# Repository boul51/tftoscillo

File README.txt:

This project is meant to make a pocket oscillator from an Arduino Due board along with a TFT screen.

To build,clean and run the project,
use associated Makefile targets in tftoscillo subfolder:
make, make clean, make run

You must have arduino-cli in your path (available from https://github.com/arduino/arduino-cli.git)

Note: Arduino IDE cannot be used to build the project because the libraries are not in the standard path,
and requires some extra defines to be set (SERIAL_IFACE=Serial or SERIAL_IFACE_SerialUSB and SERIALCOMMAND_HARDWAREONLY)
To overcome the libraries issue, you can add links to the folders in lib folder in your ~/Arduino/libraries folder,
but I don't know how to set those defines globally from the Arduino IDE.

To edit project in qtCreator :
 - cd tftoscillo
 - qtcreator tftoscillo.pro
 - select at least one kit in "Configure Project"
 - in build settings:
   - disable shadow build
 - in run settings:
   - enable run in terminal option

You should then be able to build and run the project from qtcreator

Check Makefile for additional options (in particular SERIAL_IFACE and DEBUG_CMD)

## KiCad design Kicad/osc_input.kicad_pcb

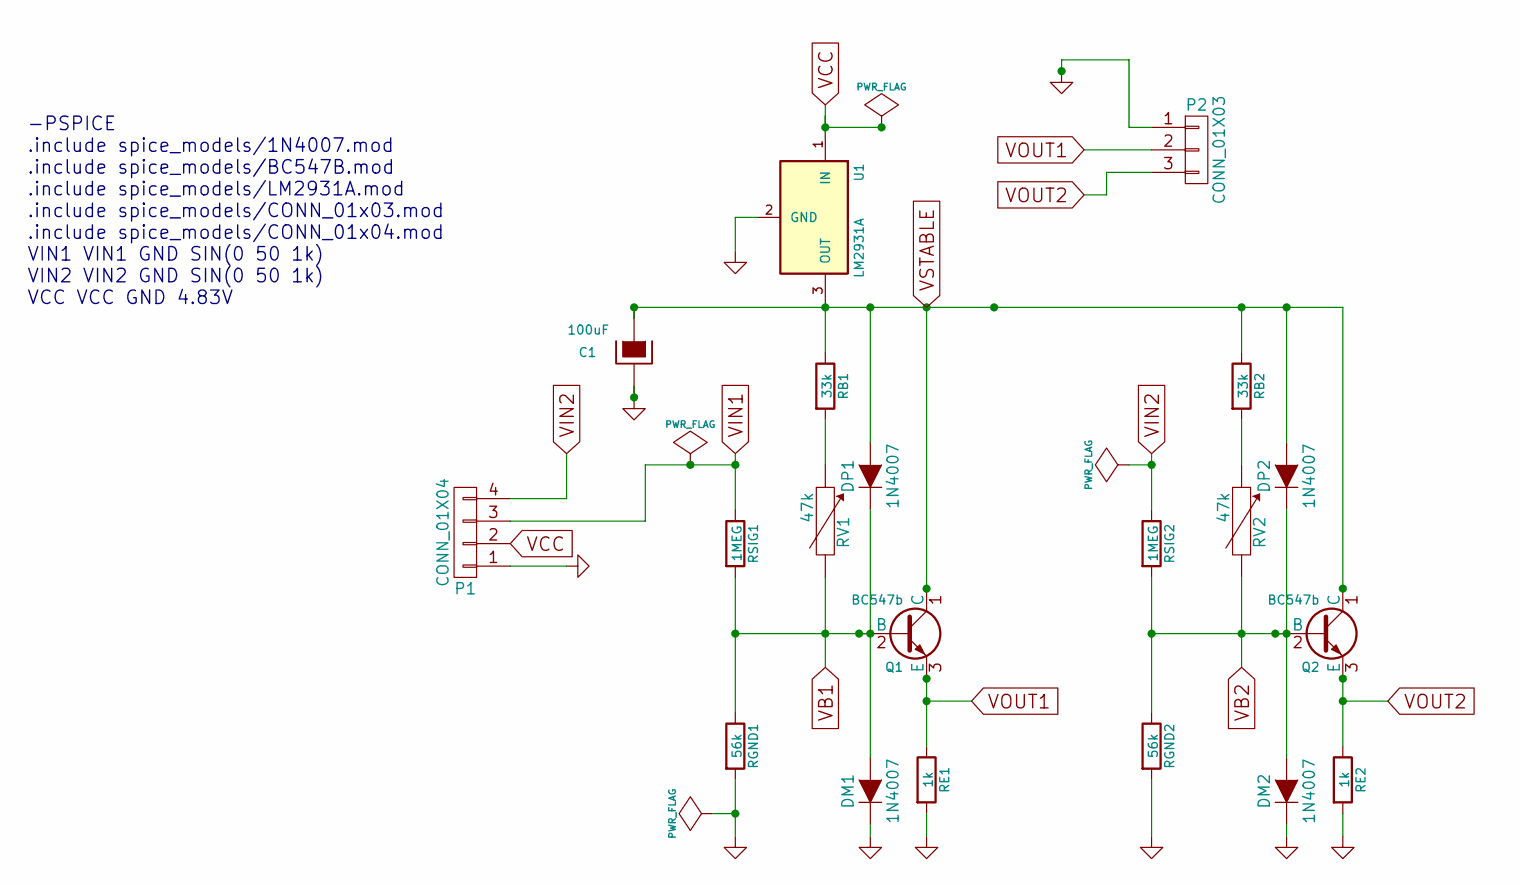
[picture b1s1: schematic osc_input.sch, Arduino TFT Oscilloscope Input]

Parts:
C1: 100uF; C_Radial_D10_L20_P5
DM1, DM2: 1N4007; Diode-DO41
DP1, DP2: 1N4007; Diode-DO41
P1: CONN_01X04; PinHeader_x4
P2: CONN_01X03; PinHeader_x3
Q1: BC547b; TO-92_1
Q2: BC547b; TO-92_2
RB1, RB2: 33k; Resistor_Horizontal_RM10mm
RE1, RE2: 1k; Resistor_Horizontal_RM10mm
RGND1, RGND2: 56k; Resistor_Horizontal_RM10mm
RSIG1, RSIG2: 1MEG; Resistor_Horizontal_RM10mm
RV1, RV2: 47k; Pot_5x8mm
U1: LM2931A; TO-220_Neutral123_Vertical

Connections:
GND: C1.2, DM1.1 (K), DM2.1 (K), P1.1, P2.1, RE1.2, RE2.2, RGND1.2, RGND2.2, U1.2 (GND)
unnamed: RB1.2, RV1.1
unnamed: RB2.2, RV2.1
VB1: DM1.2 (A), DP1.1 (K), Q1.2 (B), RGND1.1, RSIG1.2, RV1.2
VB2: DM2.2 (A), DP2.1 (K), Q2.2 (B), RGND2.1, RSIG2.2, RV2.2
VCC: P1.2, U1.1 (IN)
VIN1: P1.3, RSIG1.1
VIN2: P1.4, RSIG2.1
VOUT1: P2.2, Q1.3 (E), RE1.1
VOUT2: P2.3, Q2.3 (E), RE2.1
VSTABLE: C1.1, DP1.2 (A), DP2.2 (A), Q1.1 (C), Q2.1 (C), RB1.1, RB2.1, U1.3 (OUT)

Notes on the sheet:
-PSPICE .include spice_models/1N4007.mod .include spice_models/BC547B.mod .include spice_models/LM2931A.mod .include spice_models/CONN_01x03.mod .include spice_models/CONN_01x04.mod VIN1 VIN1 GND SIN(0 50 1k) VIN2 VIN2 GND SIN(0 50 1k) VCC VCC GND 4.83V

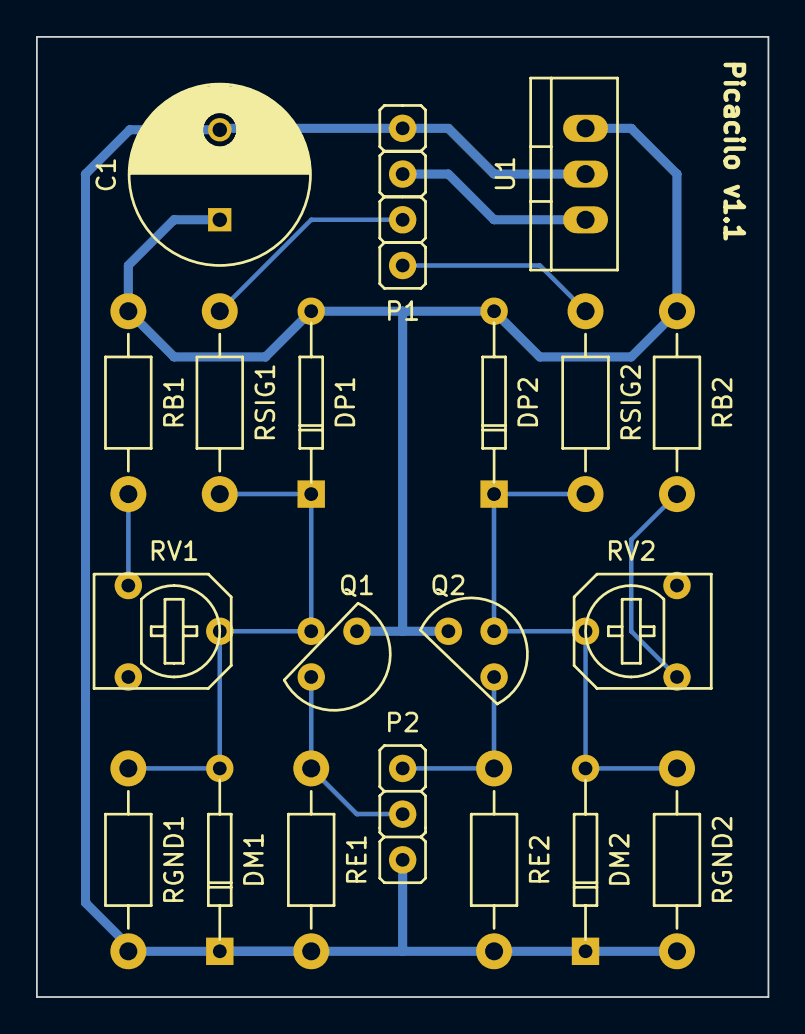
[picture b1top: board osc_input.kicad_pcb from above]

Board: 2 copper layers, 40.6 x 53.3 mm, 20 parts (0 on the bottom side), 11 nets.

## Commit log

2014-11-07 Trigger OK.
2014-11-07 Use two buffers to clear screen.
2014-11-10 Use DMA for function generator.
2014-11-11 Separate trigger / swapBuffer.
2014-11-11 Gen signals OK. Temp commit before clean.
2014-11-11 OK with external lib.
2014-11-13 Get freq from pot.
2014-11-17 Tmp commit before AdcDma integration.
2014-11-20 Added DAC and ADC DMA libs to repo.
2014-11-20 Added link files. Refactored tftoscillo.ino.
2014-11-20 Moved GenSigDma.txt to his new house.
2014-11-21 Added build script.
2014-11-21 Added AdcDma function to check trigger sample.
2014-11-22 Improved scripts.
2014-11-22 AdcDma: Small fixes (warnings, ...)
2014-11-22 GenSigDma: Allow use of debug macros with AdcDma. Needs more fixes.
2014-11-22 AdcDma: Fixed trigger timeout bug. Fixed compilation warnings.
2014-11-22 GenSigDma: Fixed compilation warnings.
2014-11-23 Added script to configure stty.
2014-11-23 AdcDma: Bug fix in findTriggerSample.
2014-11-23 GenSigDma: Small fixes.
2014-11-23 GenSigDma: Set max sample rate to 1.5 MHz (bad things happen to the signal at 2 MHz !)
2014-11-23 Use SerialCommand library.
2014-11-25 Fixed indentation.
2014-11-30 Build scripts compatible with qtcreator.
2014-11-30 Added qtCreator project.
2014-11-30 Improvements in display.
2014-11-30 Added gitignore file.
2014-11-30 Bug fixes. Added waveform serial command handler.
2014-11-30 Cleaned WaveForm enum and Stats struct in GenSigDma.
2014-12-02 Added grid. Added alternate erase method (looks better).
2014-12-02 Adjusted run.sh to run in xterm, and kill running session.
2014-12-02 Changed trigger arrow direction and color. Moved to a function.
2014-12-02 Commented out drawBegin().
2014-12-04 Fixed line endings. Check in GenSigDma::Start that a valid waveform is present.
2014-12-07 Rewrite on AdcDma. Added LibDbg.
2014-12-13 Improved scope slow mode: get SR and freq pot values while sampling. Bug fixes.
2014-12-13 Improved grid drawing. Don't update pots in slow mode for first samples.
2014-12-13 Added trigger status.
2014-12-14 Removed trigger serial logs.
2014-12-15 Moved PF definition to LibDbg.h. Added margin for grid drawing.
2014-12-15 Clean in AdcDma.
2014-12-15 Added trigger to slow mode.
2014-12-15 Multi channel in progress, needs debug.
2014-12-15 Scope OK in multi channel (tested with up to 4 channels) in fast mode.
2014-12-15 Multi channel OK in slow mode.
2014-12-19 Use g_minY and g_maxY to draw trigger arrow.
2014-12-19 SetTimerChannel now working for GenSigDma.
2014-12-22 Fixed small bug in drawSlow().
2014-12-22 Added ADCDMA API documentation.
2014-12-22 Updated AdcDma API.txt file. Added regs.txt.
2014-12-22 Added TestAdcDma files.
2014-12-22 AdcDma: bug fixes, OK with testAdcDma.
2014-12-22 AdcDma: Moved GetCaptureState() from AdcDma.h to AdcDma.cpp. Seems to fix bug in infinite loop !
2014-12-22 testAdcDma: Fixed build issues.
2014-12-27 tftoscillo: Big rewrite to use AdcDma rxHandler.
2014-12-27 tftoscillo: Set back serial command handlers.
2014-12-28 Cleaning up.
2014-12-28 tftoscillo: Handling of channel number serial command OK.
2014-12-28 tftoscillo: Bug fix when going from slow to fast mode.
2014-12-28 tftoscillo: Display framerate.
2014-12-28 tftoscillo: Fixed double drawErase bug.
2014-12-28 AdcDma: Don't re-allocate buffers if not needed.
2014-12-30 AdcDma: Removed memset call when allocating buffers.
2014-12-30 tftoscillo: Improved trigger arrow management.
2014-12-30 tftoscillo: Improve buffers size calculation to maximize sample rate.
2014-12-30 tftoscillo: Improved grid drawing in fast mode (draw grid while drawing samples).
2015-03-31 tftoscillo: Changed ios definitions to fit new connector. Added backlight handler. Added screen rotation.
2015-03-31 tftoscillo: Changes to prepare scope sample rate modifications.
2015-04-01 AdcDma: Added setChanelGain function.
2015-04-01 tftoscillo: Few fixes, display freq in s/div.
2015-04-01 tftoscillo: Removed scope rate handler. Added cbPortVarChanged (not used for now).
2015-04-01 tftoscillo: Clean in potVars handling.
2015-04-02 tftoscillo: V/div OK.
2015-12-27 Added Kicad files.
2015-12-27 ADCDMA: Removed debug logs.
2015-12-27 Added calibration handler.
2015-12-27 GenSigDma: Fixed typo in comments.
2015-12-27 Updated .gitignore for project file.
2015-12-27 Added link from tftoscillo to run.sh
2015-12-27 Updated for arduino 1.6.7
2015-12-27 Removed .pro.user from git index.
2015-12-27 Removed qtCreator user file.
2015-12-27 A bit of clean
2015-12-27 Clean, added README.txt
2015-12-27 Set board name in build script.
2015-12-27 Removed include of <avr/dtostrf.h>
2015-12-27 Updated run information.
2015-12-28 Fixed build warnings. Added clean.sh
2015-12-28 Added instructions about clean.sh in README.txt
2015-12-28 Moved README.txt to root folder.
2015-12-28 Modified README to fit root directory.
2015-12-28 Added specific SAM include directories to qtCreator project files.
2015-12-29 Fixed initial sample rate when starting at 500ms/div
2015-12-30 Bug fixes in slow mode. Removed FPS display.
2015-12-30 Bug fixes
2015-12-31 Added trigger selection and global gain serial handlers.
2016-12-12 Kicad: Updated to fit kicad version 4.0.4. Modified routing for next prototype.
2016-12-12 Kicad: Added boul51 kicad lib versions reminder.
2016-12-12 Kicad: Added gitignore Updated text properties in pcb Use lib from boul51.lib (removed components_sch.lib)
2016-12-12 Kicad: Updated cache library.
2016-12-14 Kicad: Updated schematics to use kicad embedded spice simulator.
2016-12-14 Better gain management.
2021-09-19 Use submodules, update Makefile
2021-09-19 Fork ArduinoSerialCommand to allow setting SERIALCOMMAND_HARDWAREONLY from command line
2021-09-19 Be less verbose
2021-09-30 Enable -Wall
2021-09-30 Update ArduinoSerialCommand, add Arduino-PrintStream submodule, use native USB interface for debug
    The native USB interface is much faster to write the program to the board,
    allow using it in the logs and serial commands, using SerialUSB instead of Serial
2021-09-30 Link tftoscillo to run.sh
2021-09-30 Update ArduinoSerialCommand, TFT (fix build warnings)
2021-09-30 Use CURDIR instead of PWD in Makefile
2021-11-13 Add LIBDBG_ENABLE variable to Makefile
2021-11-13 Fix crash in slow mode
2021-11-13 Replace \r\n by \n in debug logs
2021-11-13 Cleanup and add comment in mapBufferValues
2021-11-20 Add MemoryFree library to print available memory on startup
2021-11-20 Add logger submodules
2021-11-20 Add submodules for OscDisplay and OscDisplayDriver (stubs)
2021-11-21 Fix serial port initialization in Makefile
2021-11-21 Use arduino-logger for logging
2021-11-21 Remove useless SPI include
2021-12-20 Temp commit
